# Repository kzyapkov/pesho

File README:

Pesho is the gatekeeper of initlab.org

Nice GPIO map
http://azug.minpet.unibas.ch/~lukas/bricol/olinuxino-imx233/index.html#GPIO

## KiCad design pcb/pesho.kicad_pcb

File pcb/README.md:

# Pesho PCB

### Hardware description:

 * Raspberry Pi
 * 3 optoizolated relays
 * 3 optoizolated inputs
 * pesho's pcb

### Design

The design is done using latest version of KiCAD from the repository.
All modules, that weren't available are in pesho.pretty folder.

### License: [Beerware][1]

```
/*
 * ----------------------------------------------------------------------------
 * "THE BEER-WARE LICENSE" (Revision 42):
 * <phk@FreeBSD.ORG> wrote this file. As long as you retain this notice you
 * can do whatever you want with this stuff. If we meet some day, and you think
 * this stuff is worth it, you can buy me a beer in return Poul-Henning Kamp
 * ----------------------------------------------------------------------------
 */
```

[1]: http://en.wikipedia.org/wiki/Beerware

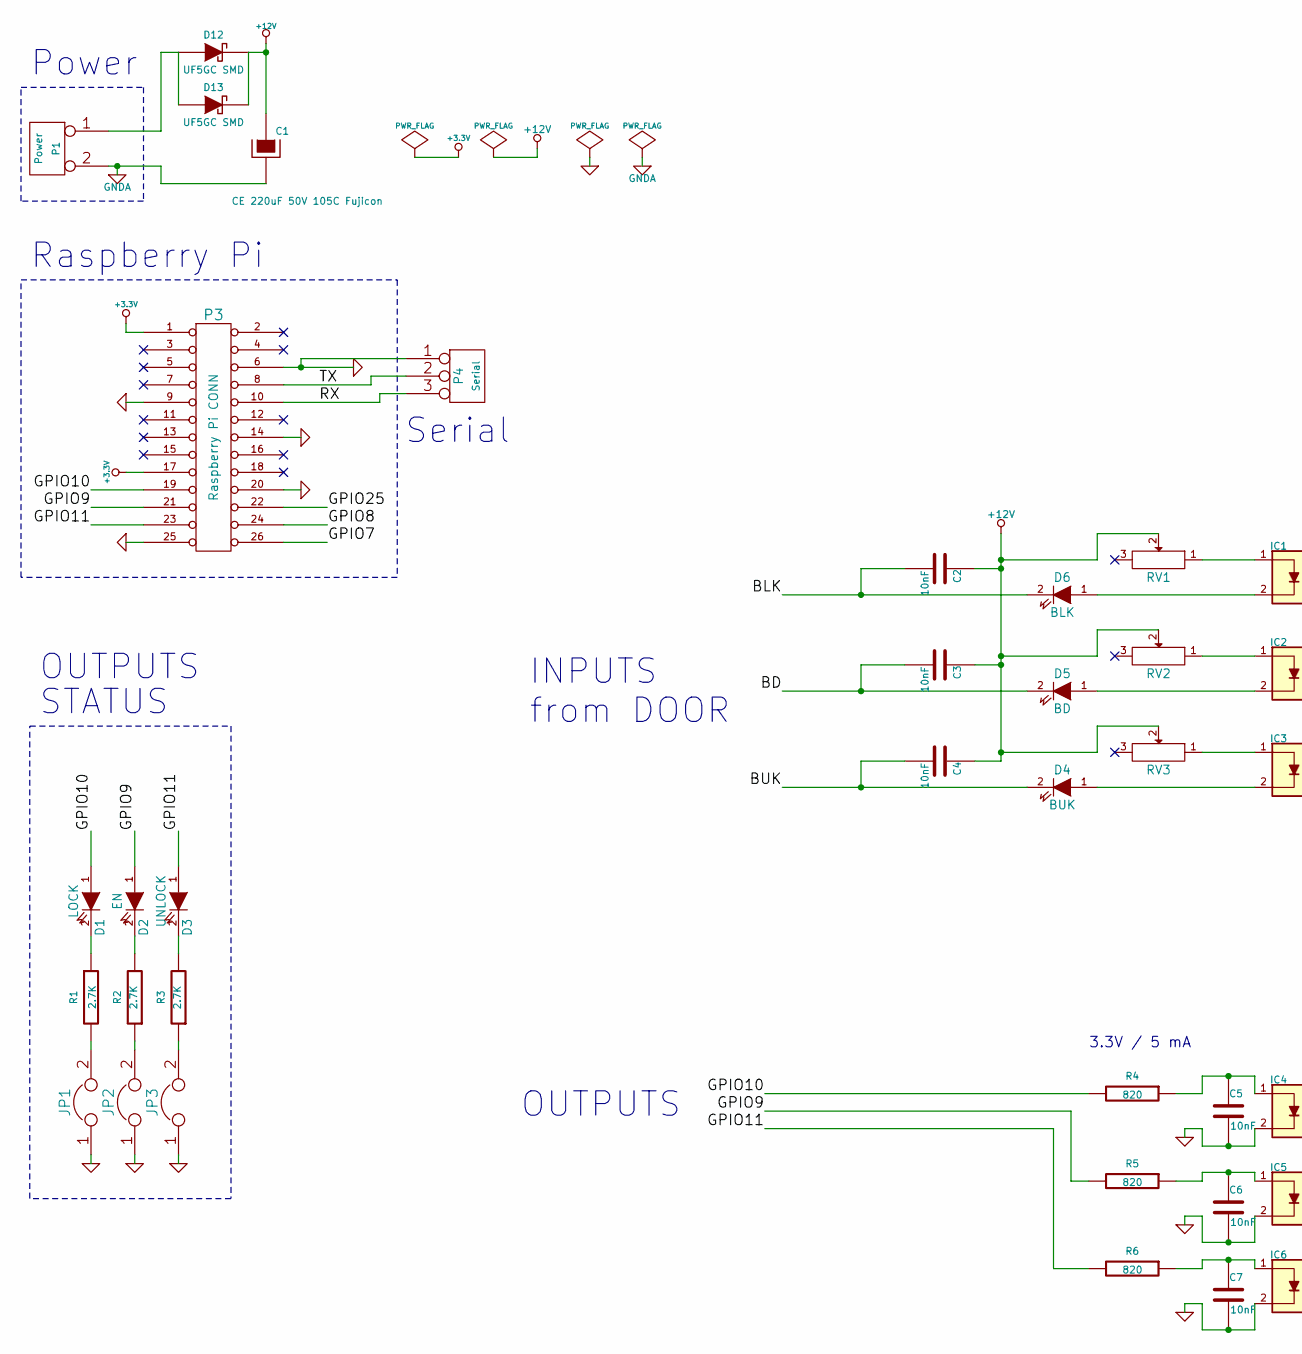
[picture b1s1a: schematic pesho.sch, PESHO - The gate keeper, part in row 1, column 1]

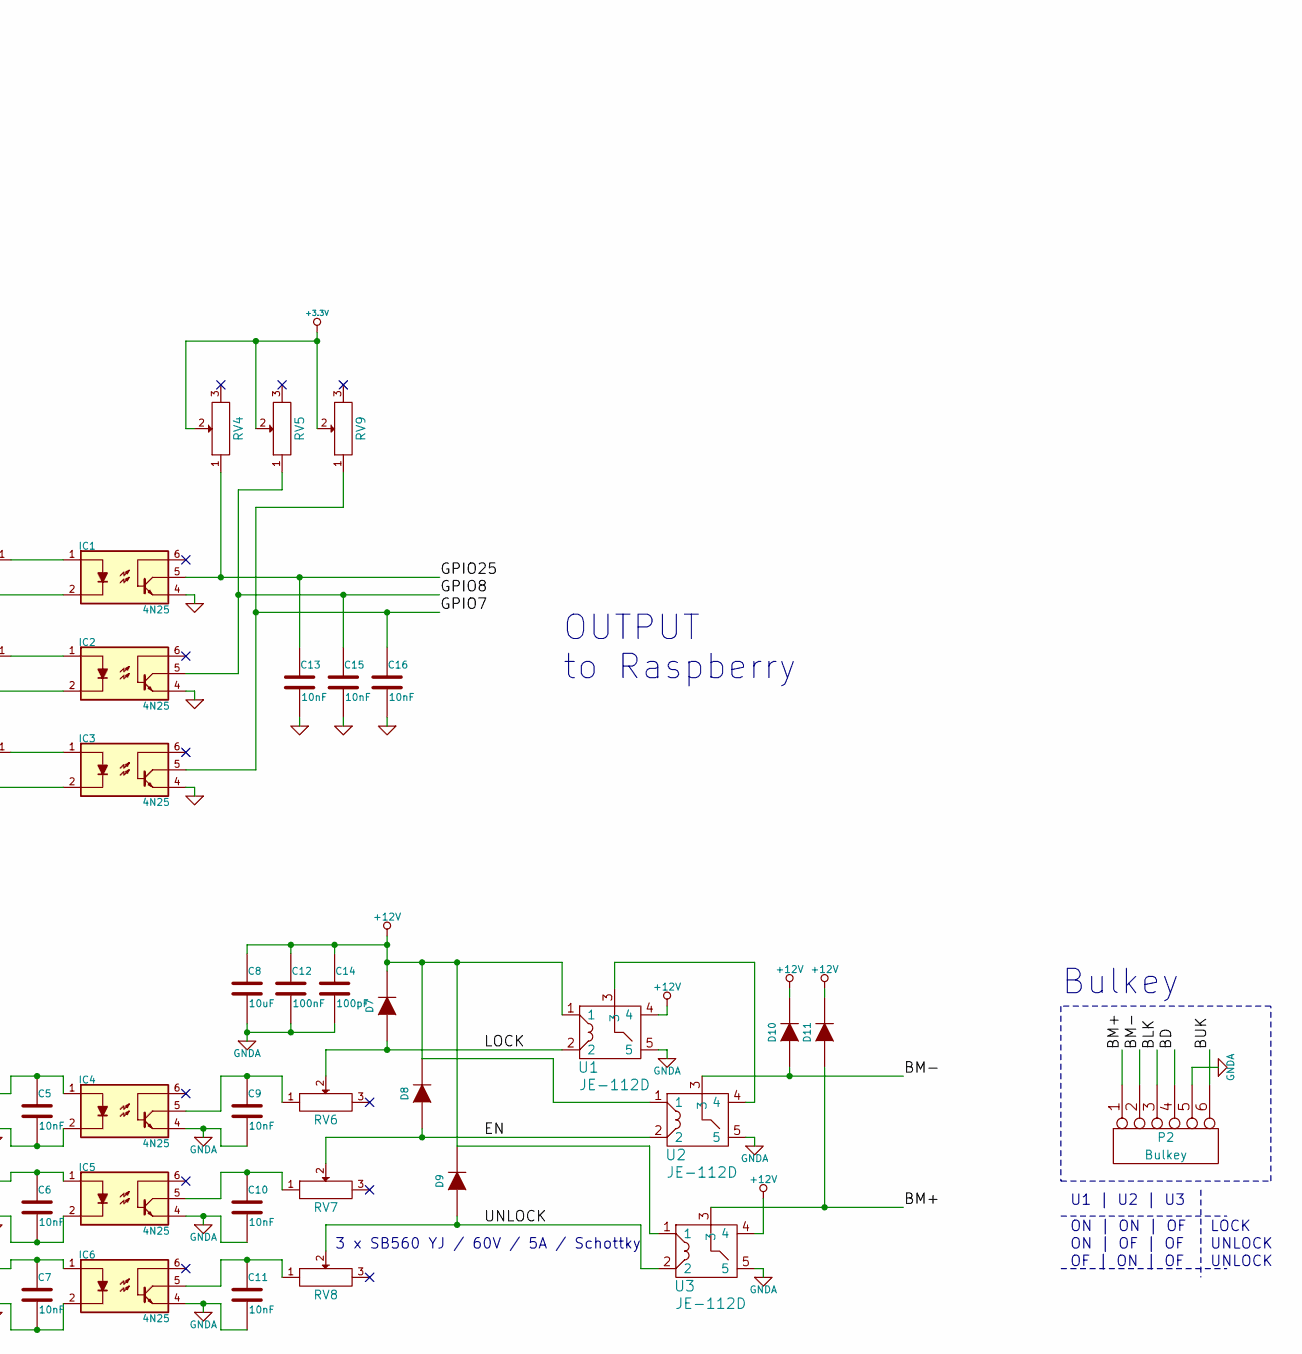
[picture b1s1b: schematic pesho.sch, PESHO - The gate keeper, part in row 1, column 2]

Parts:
C1: CE 220uF 50V 105C Fujicon; CP_10x13mm
C2, C3, C4, C5, C6, C7, C9, C10, C11, C13, C15, C16: 10nF; c_1206
C8: 10uF; c_1206
C12: 100nF; c_1206
C14: 100pF; c_1206
D1: LOCK; LED-5MM
D2: EN; LED-5MM
D3: UNLOCK; LED-5MM
D4: BUK; LED-5MM
D5: BD; LED-5MM
D6: BLK; LED-5MM
D7, D8, D9: SB560 YJ / 60V / 5A / Schottky; D3
D10, D11: SB560 YJ / 60V / 5A / Schottky; D6.5
D12, D13: UF5GC SMD; DO-214AB
IC1, IC2, IC3, IC4, IC5, IC6: 4N25; DIP-6__300_ELL
JP1, JP2, JP3: JUMPER; PIN_ARRAY_3X1
P1: Power; HD-515R-2P
P2: Bulkey; HD-515R-6P
P3: Raspberry Pi CONN; HE10_26D
P4: Serial; SIL-3
R1, R2, R3: 2.7K; c_1206
R4, R5, R6: 820; c_1206
RV1, RV2, RV3, RV4, RV5, RV6, RV7, RV8, RV9: 3296W(64W) 20K DIV; 3968W
U1, U2, U3: JE-112D

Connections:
+3.3V: P3.1, P3.17, RV4.2, RV5.2, RV9.2
+12V: C1.1, C2.1, C3.1, C4.1, C8.1, C12.1, C14.1, D7.2 (K), D8.2 (K), D9.2 (K), D10.2 (K), D11.2 (K), D12.2 (K), D13.2 (K), RV1.2, RV2.2, RV3.2, U1.1, U1.4, U2.1, U3.1, U3.4
/BD: C3.2, D5.2 (K), P2.4
/BLK: C2.2, D6.2 (K), P2.3
/BM+: D11.1 (A), P2.1, U3.3
/BM-: D10.1 (A), P2.2, U2.3
/BUK: C4.2, D4.2 (K), P2.6
/EN: D8.1 (A), RV7.2, U2.2
/GPIO7: C16.1, IC3.5, P3.26 (P22), RV9.1
/GPIO8: C15.1, IC2.5, P3.24 (P20), RV5.1
/GPIO9: D2.1 (A), P3.21, R5.2
/GPIO10: D1.1 (A), P3.19, R4.2
/GPIO11: D3.1 (A), P3.23, R6.2
/GPIO25: C13.1, IC1.5, P3.22, RV4.1
/LOCK: D7.1 (A), RV6.2, U1.2
/RX: P3.10, P4.3
/TX: P3.8, P4.2 (PM)
/UNLOCK: D9.1 (A), RV8.2, U3.2
GND: C5.2, C6.2, C7.2, C13.2, C15.2, C16.2, IC1.4, IC2.4, IC3.4, IC4.2, IC5.2, IC6.2, JP1.1, JP2.1, JP3.1, P3.6, P3.9, P3.14, P3.20, P3.25 (P24), P4.1
GNDA: C1.2, C8.2, C9.2, C10.2, C11.2, C12.2, C14.2, IC4.4, IC5.4, IC6.4, P1.2 (PM), P2.5, U1.5, U2.5, U3.5
unnamed: C5.1, IC4.1, R4.1
unnamed: C6.1, IC5.1, R5.1
unnamed: C7.1, IC6.1, R6.1
unnamed: C9.1, IC4.5, RV6.1
unnamed: C10.1, IC5.5, RV7.1
unnamed: C11.1, IC6.5, RV8.1
unnamed: D1.2 (K), R1.1
unnamed: D2.2 (K), R2.2
unnamed: D3.2 (K), R3.2
unnamed: D4.1 (A), IC3.2
unnamed: D5.1 (A), IC2.2
unnamed: D6.1 (A), IC1.2
unnamed: D12.1 (A), D13.1 (A), P1.1
unnamed: IC1.1, RV1.1
unnamed: IC2.1, RV2.1
unnamed: IC3.1, RV3.1
unnamed: JP1.2, R1.2
unnamed: JP2.2, R2.1
unnamed: JP3.2, R3.1
unnamed: U1.3, U2.4

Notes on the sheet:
3.3V / 5 mA
Raspberry Pi
3 x SB560 YJ / 60V / 5A / Schottky
Bulkey
INPUTS from DOOR
OUTPUTS
Power
U1 | U2 | U3
ON | ON | OF
ON | OF | OF
OF | ON | OF
LOCK
UNLOCK
Serial
STATUS
OUTPUT to Raspberry

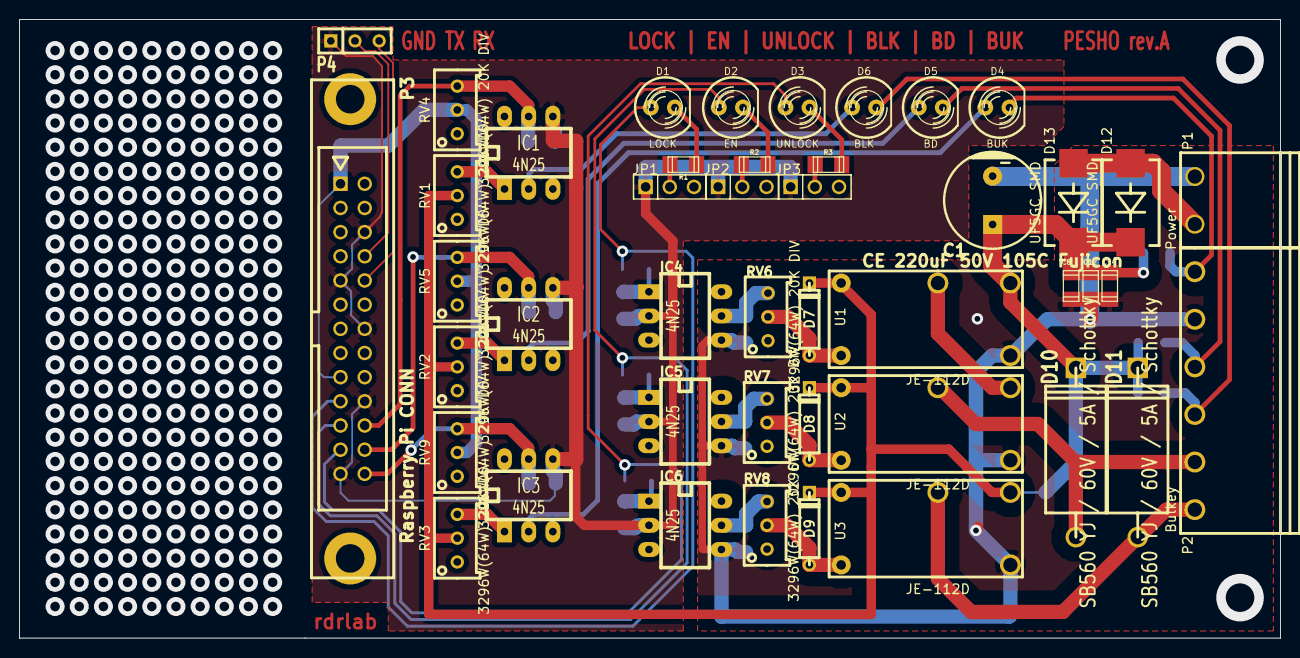
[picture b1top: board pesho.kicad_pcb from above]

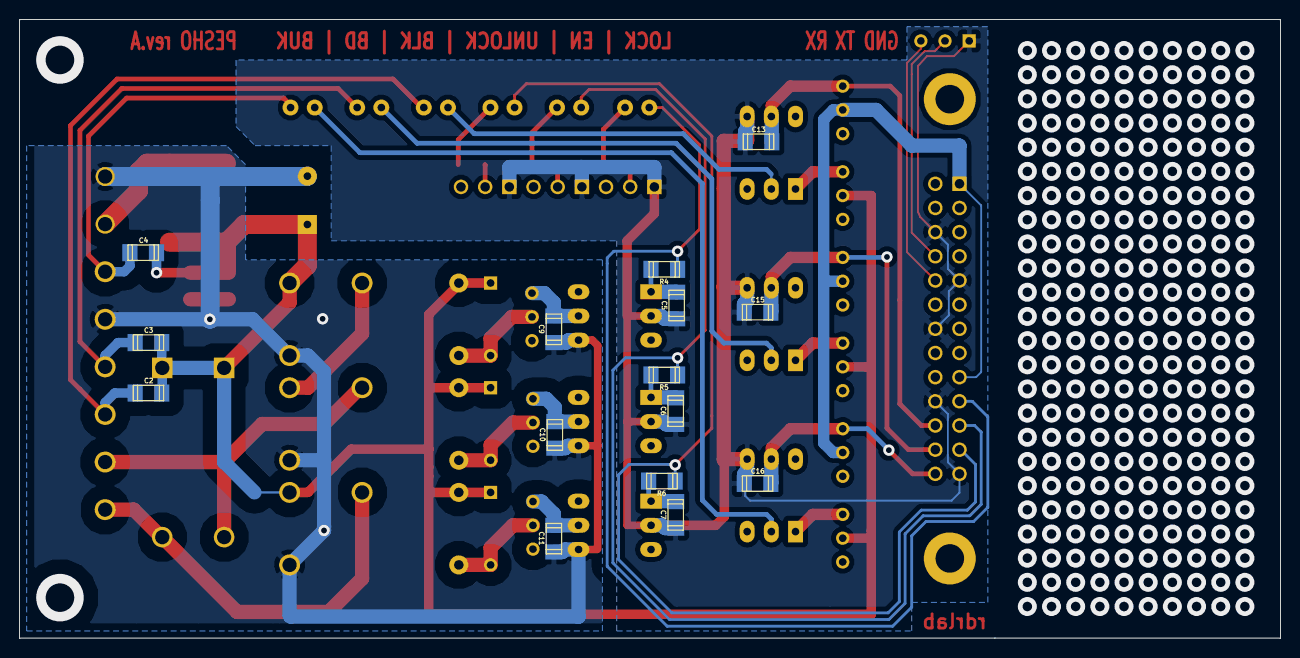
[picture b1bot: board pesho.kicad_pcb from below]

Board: 2 copper layers, 132.5 x 65.0 mm, 60 parts (15 on the bottom side), 40 nets.

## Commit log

2014-09-02 initial
2014-09-03 Basisc, GPIO monitor
2014-09-04 Door controller logic improvements
2014-09-04 markdown, lincense
2014-09-04 all config structs in config.go
2014-09-04 GOMAXPROCS=1
2014-09-04 door state machine spaghetti
2014-09-04 Fix missing config path log
2014-09-05 more wip
2014-09-05 refactored state machine
2014-09-05 Door: public interface
2014-09-06 State pretty print
2014-09-06 Protect State and other fixes
2014-09-06 Remove old implementation of door
2014-09-06 some documentation
2014-09-07 Comments
2014-09-07 logging and shit
2014-09-12 refactored, simpler logic, web and buttons
2014-09-12 test fixes
2014-09-16 Ignore all .bak and autosave files
2014-09-16 Initial commit of the PCB.
2014-09-16 Fix the view of the license.
2014-09-16 ignore PCB backup files
2014-09-16 added test pcb segment
2014-09-17 ignore *.bak files
2014-09-17 better layout and all components on place
2014-09-30 added some traces
2014-09-30 Diode 60V / 5A module added to the library.
2014-09-30 2 serial diodes added for protection.
2014-10-01 Final version of the pcb.
2014-10-03 don't include .zip files into the repo.
2014-10-03 Latest layout submitted to bulged for films.
2014-10-03 Include libraries description file.
2014-10-03 Schematic and layout .pdf files submitted to bulged.
2014-10-03 BOM added to the repository.
2014-10-06 Last version with fixed drills and send for production.
2014-10-06 Gerber files send to CPR for production.
2014-10-08 Fixed small bug in the pcb on one of the Relays.
2014-10-29 Latest updates to the PCB included
2014-11-03 Found like this after weeks of inactivity.
2014-11-12 Schematic retought and resistor values changed.
2014-12-10 Last update ! The PCB is not working, because of the relays.
2014-12-14 yet another hw version
2014-12-14 more hw files
2014-12-15 changed values of the resistors and added connections to the rpi
2014-12-15 ignore kicad cache and backup files
2014-12-15 simple open loop logic, new pin layout
2014-12-16 some explanations
2014-12-16 moved stuff around
2015-01-25 button pin numbers
2015-01-25 config, logging
2015-01-25 systemd.service file
2015-03-03 fix buttons and inputs
2015-03-03 web key
2015-03-03 add build instructions
2015-03-03 add useful link
2015-03-03 add todos
2015-03-03 Unlock even if door is open, other minor fixes
2015-04-03 #1 web notifications
2015-04-03 remove a todo item
2015-05-01 add token parameter for web notifications, #2
2015-05-01 remove unused chan
2015-05-01 fix #4
2015-05-20 forget lastState, don't debounce inputs
2015-05-20 fix #5
2015-05-20 fix #3
